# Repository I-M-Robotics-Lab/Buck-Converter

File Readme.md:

# A Simple Buck Converter Unit with ME3121

VIN Input: 5-40V

Output: 5V 1A; 3.3V 500mA

Dimension: 22 x 17 mm

This is a very compact Buck Converter Unit that turns a wide range of input voltage into the common 5V and 3.3V. It is cheap and have better performance than LM2596.

|  |  |
|-------------------------|-----------------------------------|

## Schematics

## Order / Manufacturing

Download the `Gerber.zip` file from release and submit it to [JLCPCB](https://cart.jlcpcb.com/quote?spm=jlcpcb.Public.2006), leave everything set as default.

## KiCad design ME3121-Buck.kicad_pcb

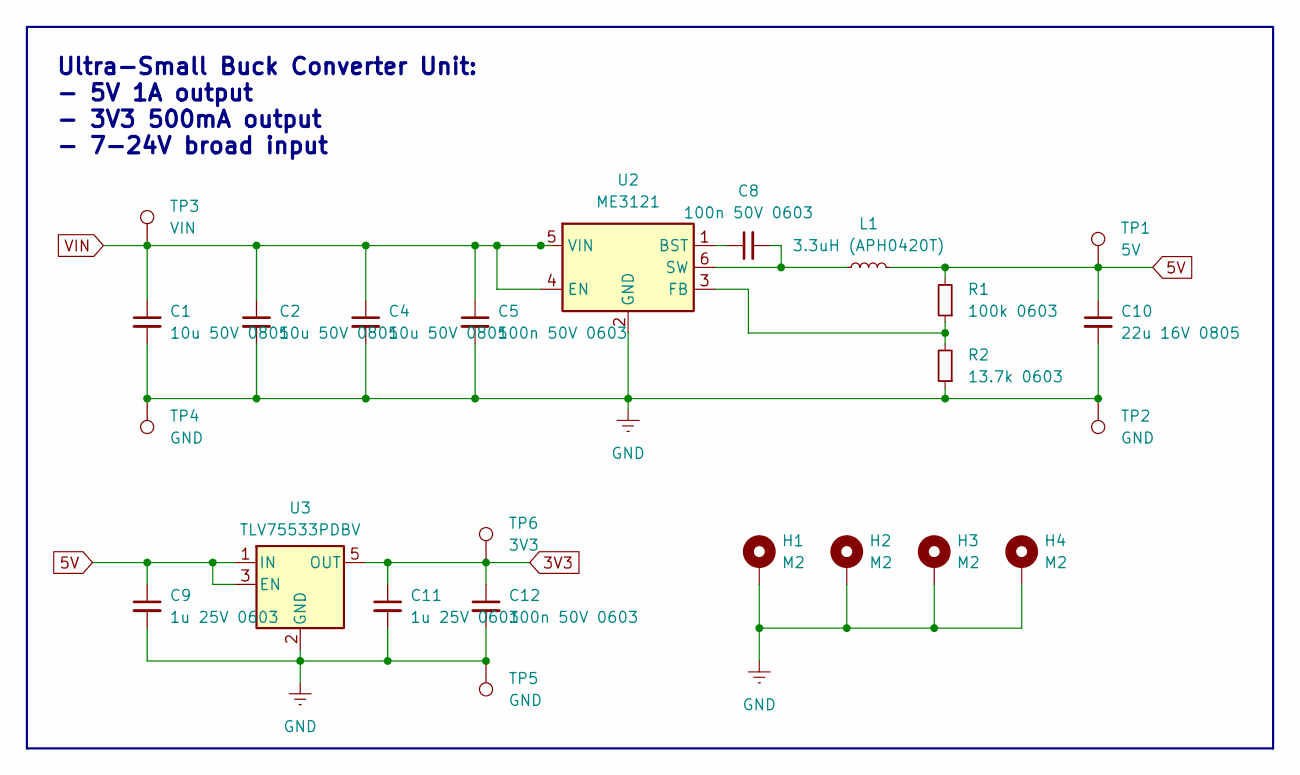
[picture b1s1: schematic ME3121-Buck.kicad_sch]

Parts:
C1, C2, C4: 10u 50V 0805; C_0805_2012Metric
C5, C8, C12: 100n 50V 0603; C_0603_1608Metric
C9, C11: 1u 25V 0603; C_0603_1608Metric
C10: 22u 16V 0805; C_0805_2012Metric
H1, H2, H3, H4: M2; MountingHole_2.2mm_M2_DIN965_Pad
L1: 3.3uH (APH0420T); L_APV_APH0420
R1: 100k 0603; R_0603_1608Metric
R2: 13.7k 0603; R_0603_1608Metric
TP1: 5V; PROBE_PAD_1206
TP2, TP4, TP5: GND; PROBE_PAD_1206
TP3: VIN; PROBE_PAD_1206
TP6: 3V3; PROBE_PAD_1206
U2: ME3121; SOT-23-6
U3: TLV75533PDBV; SOT-23-5

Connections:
3V3: C11.1, C12.1, TP6.1, U3.5 (OUT)
5V: C9.1, C10.1, L1.2, R1.2, TP1.1, U3.1 (IN), U3.3 (EN)
GND: C1.2, C2.2, C4.2, C5.2, C9.2, C10.2, C11.2, C12.2, H1.1, H2.1, H3.1, H4.1, R2.1, TP2.1, TP4.1, TP5.1, U2.2 (GND), U3.2 (GND)
unnamed: C8.1, U2.1 (BST)
unnamed: R1.1, R2.2, U2.3 (FB)
unnamed: C8.2, L1.1, U2.6 (SW)
VIN: C1.1, C2.1, C4.1, C5.1, TP3.1, U2.4 (EN), U2.5 (VIN)

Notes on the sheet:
Ultra-Small Buck Converter Unit: - 5V 1A output - 3V3 500mA output - 7-24V broad input

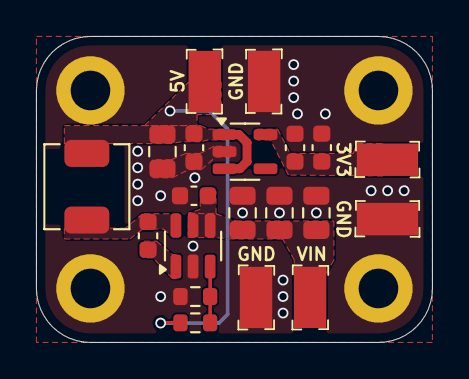
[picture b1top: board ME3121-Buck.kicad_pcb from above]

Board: 2 copper layers, 22.0 x 17.0 mm, 24 parts (0 on the bottom side), 7 nets.

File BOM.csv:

"Reference","Value","Datasheet","Footprint","Qty","DNP"
"C1,C2,C4","10u 50V 0805","~","Capacitor_SMD:C_0805_2012Metric","3",""
"C5,C8,C12","100n 50V 0603","~","Capacitor_SMD:C_0603_1608Metric","3",""
"C9,C11","1u 25V 0603","~","Capacitor_SMD:C_0603_1608Metric","2",""
"C10","22u 16V 0805","~","Capacitor_SMD:C_0805_2012Metric","1",""
"L1","3.3uH (APH0420T)","https://lcsc.com/datasheet/lcsc_datasheet_2409302232_APV-APH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","Inductor_SMD:L_APV_APH0420","1",""
"R1","100k 0603","~","Resistor_SMD:R_0603_1608Metric","1",""
"R2","13.7k 0603","~","Resistor_SMD:R_0603_1608Metric","1",""
"U2","ME3121","https://lcsc.com/datasheet/lcsc_datasheet_2203311630_MICRONE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","Package_TO_SOT_SMD:SOT-23-6","1",""
"U3","TLV75533PDBV","http://www.ti.com/lit/ds/symlink/tlv755p.pdf","Package_TO_SOT_SMD:SOT-23-5","1",""

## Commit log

2026-01-15 init
2026-01-15 gitignore
2026-01-15 Update README with output specs and images
    Added output specifications and images to the README.
2026-01-15 Rearrange images in Readme.md
2026-01-15 picture
2026-01-15 Fix image path for rendered front image in README
2026-01-15 readme
